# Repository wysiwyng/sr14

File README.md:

sr14
====

this will be the repo for the student robotics 2014 competition (http://srobo.org) of team MaI Senior (http://srobo.org/teams/MAI)

here all external hardware and software files will be stored, the main program code will be made public after the competition is over.

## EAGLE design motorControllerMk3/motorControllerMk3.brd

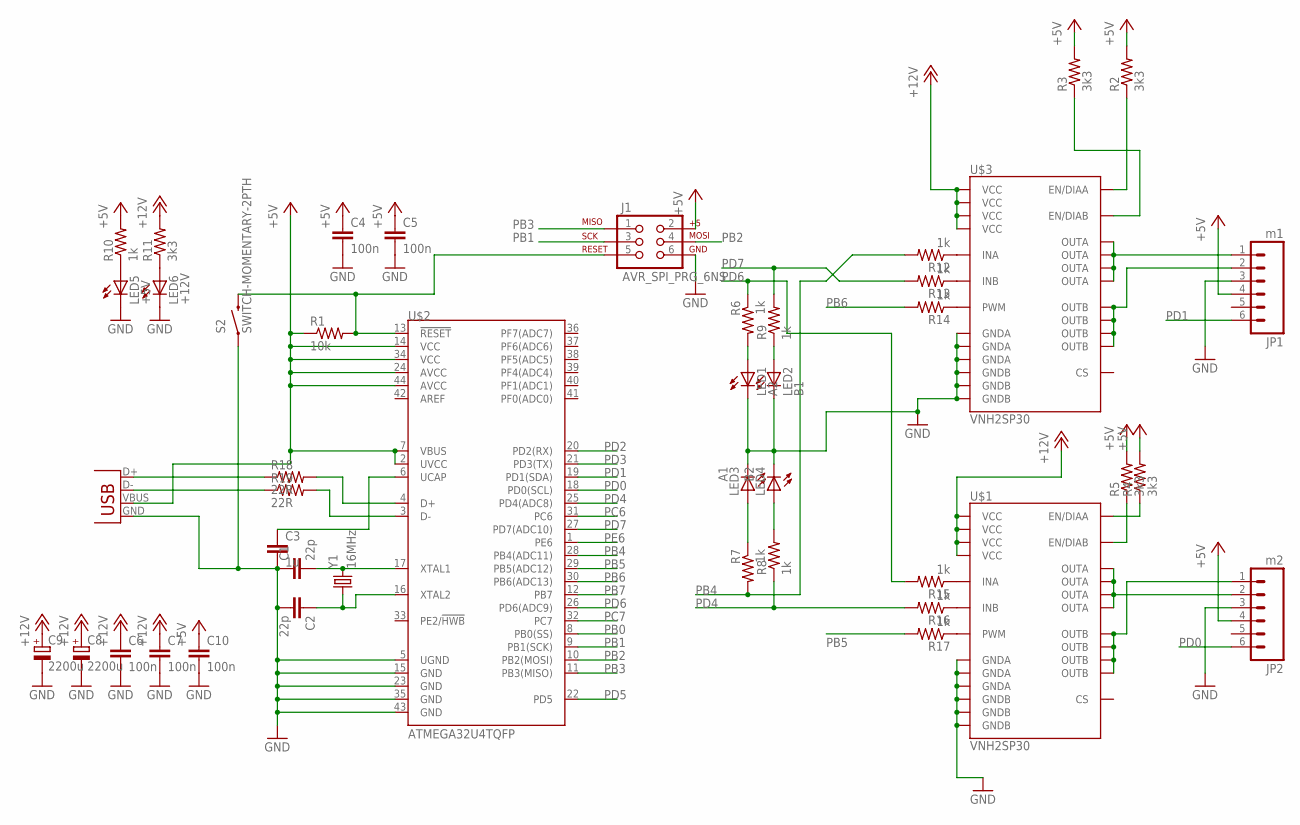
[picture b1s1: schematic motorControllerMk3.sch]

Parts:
C1, C2: 22p; 0805
C3: 1u; 0805
C4, C5, C6, C7, C10: 100n; 0805
C8, C9: 2200u; E5-8,5
J1: AVR_SPI_PRG_6NS; 2X3-NS
JP1: m1; 1X06
JP2: m2; 1X06
JP3: USB-SMD-NS; USB-MINIB-NOSTOP
LED1: A2; LED-1206
LED2: B1; LED-1206
LED3: A1; LED-1206
LED4: B2; LED-1206
LED5: +5V; LED-1206
LED6: +12V; LED-1206
R1: 10k; 0805
R2, R3, R4, R5, R11: 3k3; 0805
R6, R7, R8, R9, R10, R12, R13, R14, R15, R16, R17: 1k; 0805
R18, R19: 22R; 0805
S2: SWITCH-MOMENTARY-2PTH; TACTILE-PTH
U$1, U$3: VNH2SP30
U$2: ATMEGA32U4TQFP; SPARKFUN-DIGITALIC_TQFP44
Y1: 16MHz; HC49US

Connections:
+5V: C4.1, C5.1, C10.1, J1.2, JP1.4, JP2.4, JP3.VBUS, R1.1, R2.2, R3.2, R4.2, R5.2, R10.2, U$2.2 (UVCC), U$2.7 (VBUS), U$2.14 (VCC), U$2.24 (AVCC), U$2.34 (VCC), U$2.44 (AVCC)
+12V: C6.1, C7.1, C8.+, C9.+, R11.2, U$1.3 (VCC), U$1.13 (VCC), U$1.23 (VCC), U$1.SLUG1 (VCC), U$3.3 (VCC), U$3.13 (VCC), U$3.23 (VCC), U$3.SLUG1 (VCC)
GND: C1.1, C2.2, C3.2, C4.2, C5.2, C6.2, C7.2, C8.-, C9.-, C10.2, J1.6, JP1.3, JP2.3, JP3.GND, LED1.C, LED2.C, LED3.C, LED4.C, LED5.C, LED6.C, S2.1, U$1.18 (GNDB), U$1.19 (GNDB), U$1.20 (GNDB), U$1.26 (GNDA), U$1.27 (GNDA), U$1.28 (GNDA), U$2.5 (UGND), U$2.15 (GND), U$2.23 (GND), U$2.35 (GND), U$2.43 (GND), U$3.18 (GNDB), U$3.19 (GNDB), U$3.20 (GNDB), U$3.26 (GNDA), U$3.27 (GNDA), U$3.28 (GNDA)
unnamed: R15.1, U$1.5 (INA)
unnamed: C2.1, U$2.16 (XTAL2), Y1.1
unnamed: C1.2, U$2.17 (XTAL1), Y1.2
unnamed: C3.1, U$2.6 (UCAP)
unnamed: R16.1, U$1.11 (INB)
unnamed: R17.1, U$1.8 (PWM)
unnamed: R5.1, U$1.10 (EN/DIAB)
unnamed: R4.1, U$1.6 (EN/DIAA)
unnamed: R12.1, U$3.5 (INA)
unnamed: R18.2, U$2.4 (D+)
unnamed: R19.2, U$2.3 (D-)
unnamed: R13.1, U$3.11 (INB)
unnamed: R14.1, U$3.8 (PWM)
unnamed: JP3.D+, R18.1
unnamed: JP3.D-, R19.1
unnamed: LED3.A, R7.1
unnamed: R3.1, U$3.10 (EN/DIAB)
unnamed: LED1.A, R6.2
unnamed: R2.1, U$3.6 (EN/DIAA)
unnamed: LED4.A, R8.2
unnamed: LED5.A, R10.1
unnamed: LED6.A, R11.1
unnamed: LED2.A, R9.1
unnamed: J1.5, R1.2, S2.3 (2), U$2.13 (!RESET)
OUTA1: JP1.1, U$3.1 (OUTA), U$3.25 (OUTA), U$3.30 (OUTA), U$3.SLUG3 (OUTA)
OUTA2: JP2.2, U$1.1 (OUTA), U$1.25 (OUTA), U$1.30 (OUTA), U$1.SLUG3 (OUTA)
OUTB1: JP1.2, U$3.15 (OUTB), U$3.16 (OUTB), U$3.21 (OUTB), U$3.SLUG2 (OUTB)
OUTB2: JP2.1, U$1.15 (OUTB), U$1.16 (OUTB), U$1.21 (OUTB), U$1.SLUG2 (OUTB)
PB0: U$2.8 (PB0(SS))
PB1: J1.3, U$2.9 (PB1(SCK))
PB2: J1.4, U$2.10 (PB2(MOSI))
PB3: J1.1, U$2.11 (PB3(MISO))
PB4: R7.2, R12.2, U$2.28 (PB4(ADC11))
PB5: R17.2, U$2.29 (PB5(ADC12))
PB6: R14.2, U$2.30 (PB6(ADC13))
PB7: U$2.12 (PB7)
PC6: U$2.31 (PC6)
PC7: U$2.32 (PC7)
PD0: JP2.6, U$2.18 (PD0(SCL))
PD1: JP1.6, U$2.19 (PD1(SDA))
PD2: U$2.20 (PD2(RX))
PD3: U$2.21 (PD3(TX))
PD4: R8.1, R16.2, U$2.25 (PD4(ADC8))
PD5: U$2.22 (PD5)
PD6: R6.1, R15.2, U$2.26 (PD6(ADC9))
PD7: R9.2, R13.2, U$2.27 (PD7(ADC10))
PE6: U$2.1 (PE6)

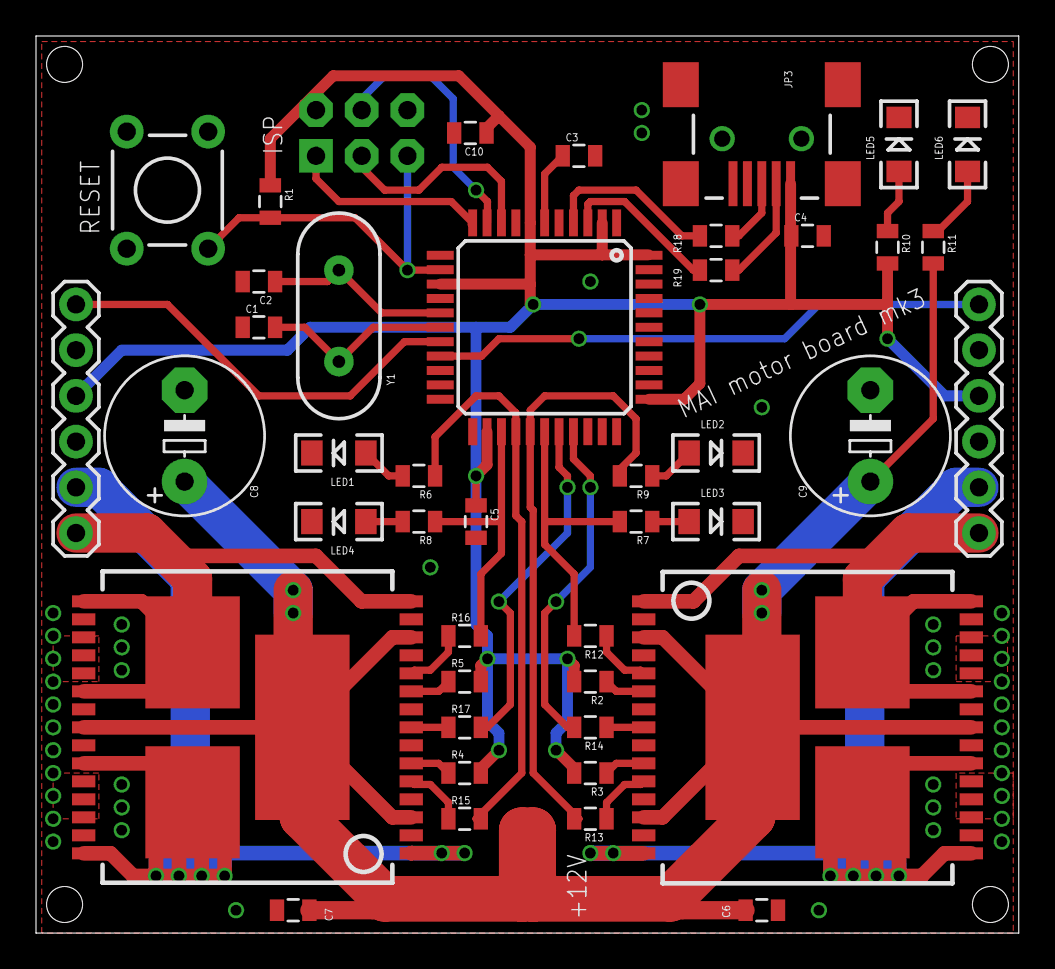
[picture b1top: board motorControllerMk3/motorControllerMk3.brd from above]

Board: 2 copper layers, 54.6 x 49.8 mm, 44 parts (0 on the bottom side), 42 nets.

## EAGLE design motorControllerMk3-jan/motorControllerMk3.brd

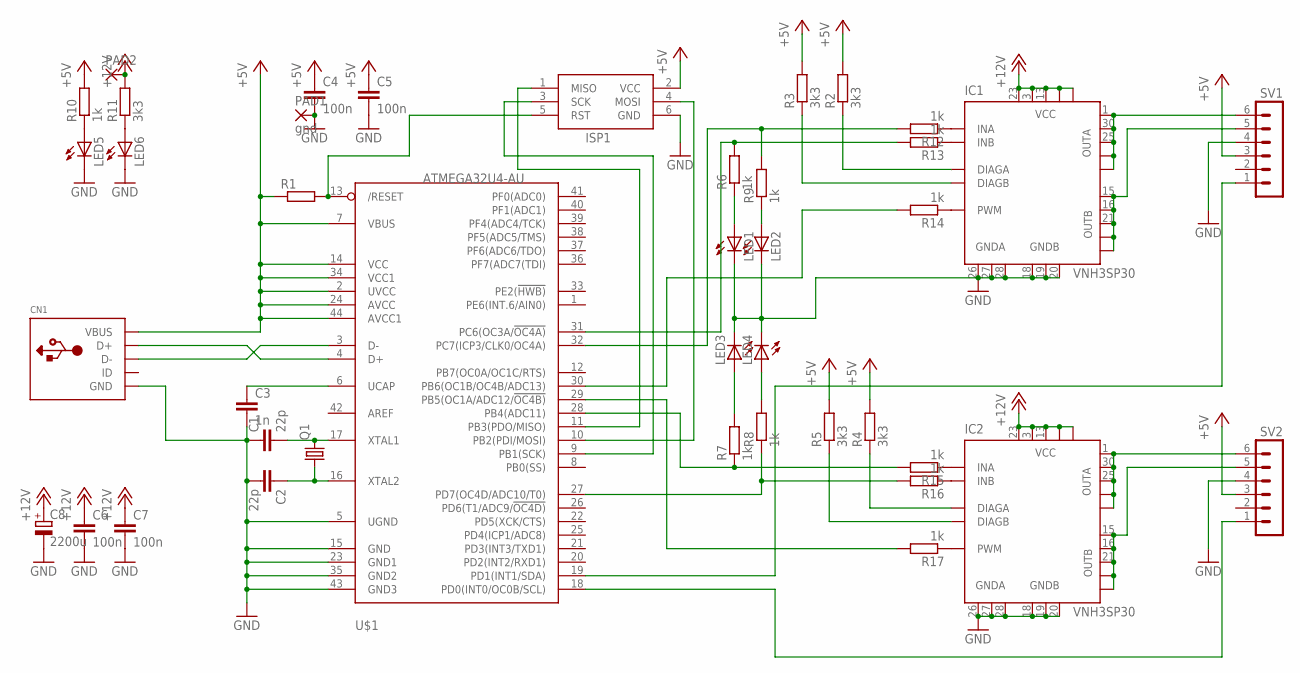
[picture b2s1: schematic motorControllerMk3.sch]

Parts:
C1, C2: 22p; C0805K
C3: 1n; C0805K
C4, C5, C6, C7: 100n; C0805K
C8: 2200u; E5-8,5
CN1: USBMINIB; USB-MINIB
IC1, IC2: VNH3SP30; MULTIPOWERSO-30
ISP1: AVRISP-6; AVRISP
LED1, LED2, LED3, LED4, LED5, LED6: LEDSML1206; SML1206
PAD1: gnd; 3,81/1,1
PAD2: 3,81/1,1
Q1: CRYSTALHC49U-V; HC49U-V
R1: R-EU_M0805; M0805
R2, R3, R4, R5, R11: 3k3; M0805
R6, R7, R8, R9, R10, R12, R13, R14, R15, R16, R17: 1k; M0805
SV1, SV2: MA06-1
U$1: ATMEGA32U4-AU; TQFP44

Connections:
+5V: C4.1, C5.1, CN1.VBUS, ISP1.2 (VCC), R1.1, R2.2, R3.2, R4.2, R5.2, R10.2, SV1.3, SV2.3, U$1.2 (UVCC), U$1.7 (VBUS), U$1.14 (VCC), U$1.24 (AVCC), U$1.34 (VCC1), U$1.44 (AVCC1)
+12V: C6.1, C7.1, C8.+, IC1.3 (VCC), IC1.13 (VCC), IC1.23 (VCC), IC1.VCC, IC1.VCC@1 (VCC), IC2.3 (VCC), IC2.13 (VCC), IC2.23 (VCC), IC2.VCC, IC2.VCC@1 (VCC), PAD2.1, R11.2
GND: C1.1, C2.2, C3.2, C4.2, C5.2, C6.2, C7.2, C8.-, CN1.GND, IC1.18 (GNDB), IC1.19 (GNDB), IC1.20 (GNDB), IC1.26 (GNDA), IC1.27 (GNDA), IC1.28 (GNDA), IC2.18 (GNDB), IC2.19 (GNDB), IC2.20 (GNDB), IC2.26 (GNDA), IC2.27 (GNDA), IC2.28 (GNDA), ISP1.6 (GND), LED1.C, LED2.C, LED3.C, LED4.C, LED5.C, LED6.C, PAD1.1, SV1.4, SV2.4, U$1.5 (UGND), U$1.15 (GND), U$1.23 (GND1), U$1.35 (GND2), U$1.43 (GND3)
unnamed: ISP1.3 (SCK), U$1.9 (PB1(SCK))
unnamed: C2.1, Q1.1, U$1.16 (XTAL2)
unnamed: C1.2, Q1.2, U$1.17 (XTAL1)
unnamed: C3.1, U$1.6 (UCAP)
unnamed: ISP1.5 (RST), R1.2, U$1.13 (/RESET)
unnamed: ISP1.4 (MOSI), U$1.10 (PB2(PDI/MOSI))
unnamed: ISP1.1 (MISO), U$1.11 (PB3(PDO/MISO))
unnamed: R17.2, U$1.29 (PB5(OC1A/ADC12/!OC4B))
unnamed: R14.2, U$1.30 (PB6(OC1B/OC4B/ADC13))
unnamed: CN1.D+, U$1.4 (D+)
unnamed: CN1.D-, U$1.3 (D-)
unnamed: SV2.1, U$1.18 (PD0(INT0/OC0B/SCL))
unnamed: IC1.1 (OUTA), IC1.25 (OUTA), IC1.30 (OUTA), IC1.OUTA, IC1.OUTA@1 (OUTA), SV1.6
unnamed: IC1.15 (OUTB), IC1.16 (OUTB), IC1.21 (OUTB), IC1.OUTB, IC1.OUTB@1 (OUTB), SV1.5
unnamed: IC2.15 (OUTB), IC2.16 (OUTB), IC2.21 (OUTB), IC2.OUTB, IC2.OUTB@1 (OUTB), SV2.5
unnamed: IC2.1 (OUTA), IC2.25 (OUTA), IC2.30 (OUTA), IC2.OUTA, IC2.OUTA@1 (OUTA), SV2.6
unnamed: SV1.1, U$1.19 (PD1(INT1/SDA))
unnamed: IC2.6 (DIAGA), R4.1
unnamed: IC2.10 (DIAGB), R5.1
unnamed: IC1.6 (DIAGA), R2.1
unnamed: IC1.10 (DIAGB), R3.1
unnamed: LED4.A, R8.2
unnamed: R8.1, R16.2, U$1.27 (PD7(OC4D/ADC10/T0))
unnamed: R7.1, R15.2, U$1.28 (PB4(ADC11))
unnamed: R6.2, R13.2, U$1.31 (PC6(OC3A/!OC4A))
unnamed: R9.2, R12.2, U$1.32 (PC7(ICP3/CLK0/OC4A))
unnamed: LED3.A, R7.2
unnamed: LED5.A, R10.1
unnamed: LED6.A, R11.1
unnamed: LED2.A, R9.1
unnamed: LED1.A, R6.1
unnamed: IC1.5 (INA), R12.1
unnamed: IC1.11 (INB), R13.1
unnamed: IC1.8 (PWM), R14.1
unnamed: IC2.5 (INA), R15.1
unnamed: IC2.11 (INB), R16.1
unnamed: IC2.8 (PWM), R17.1

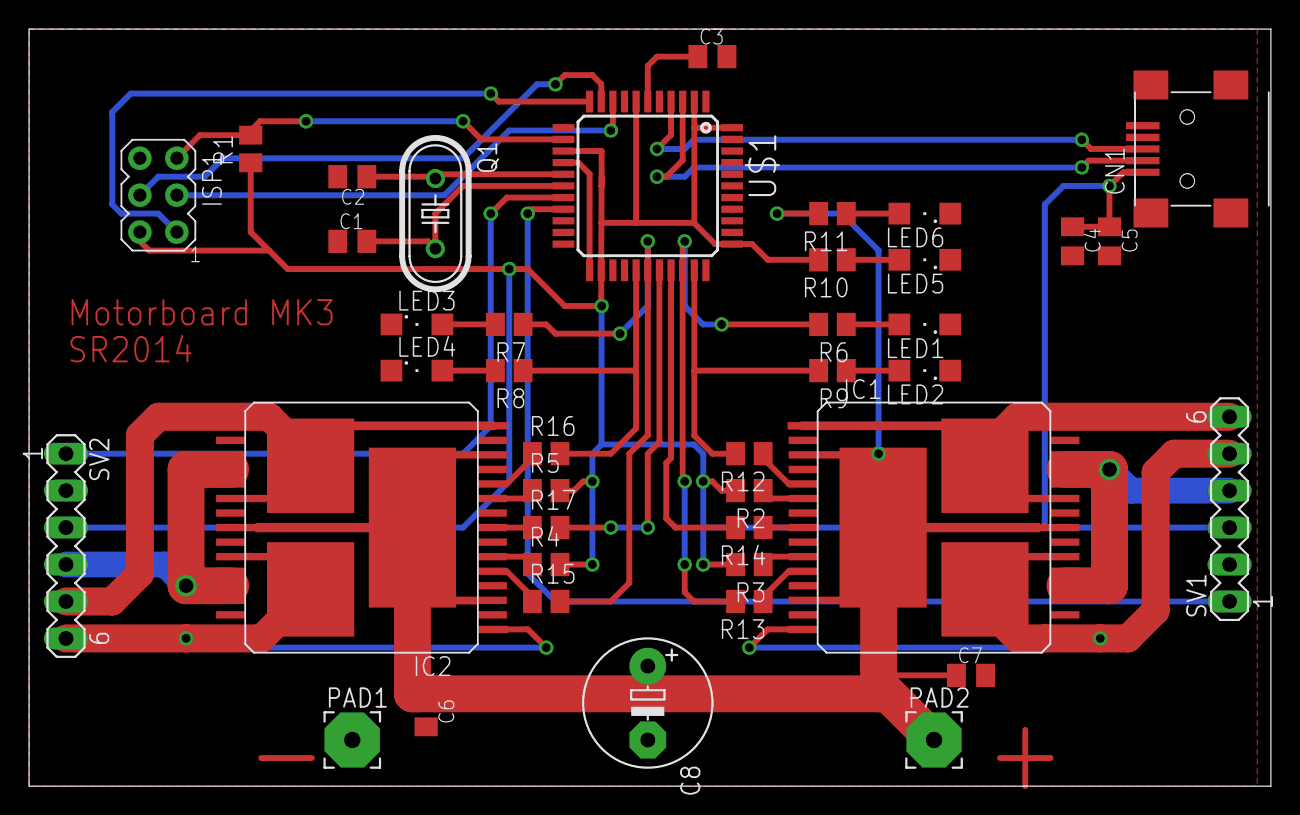
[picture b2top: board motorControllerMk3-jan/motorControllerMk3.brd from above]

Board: 2 copper layers, 85.4 x 52.1 mm, 41 parts (0 on the bottom side), 40 nets.

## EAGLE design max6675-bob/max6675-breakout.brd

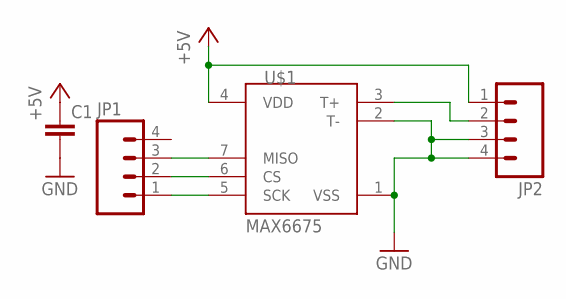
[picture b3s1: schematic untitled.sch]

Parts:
C1: CAP0805; 0805
JP1, JP2: M04LONGPADS; 1X04_LONGPADS
U$1: MAX6675; SO08-MAX6675

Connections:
+5V: C1.1, JP2.1, U$1.4 (VDD)
GND: C1.2, JP2.3, JP2.4, U$1.1 (VSS), U$1.2 (T-)
unnamed: JP1.1, U$1.5 (SCK)
unnamed: JP1.3, U$1.7 (MISO)
unnamed: JP1.2, U$1.6 (CS)
unnamed: JP2.2, U$1.3 (T+)

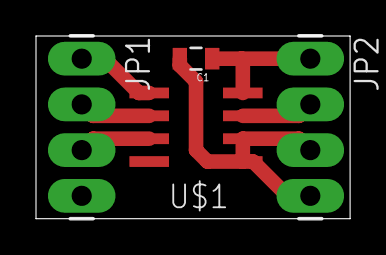
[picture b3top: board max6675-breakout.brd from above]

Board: 2 copper layers, 17.4 x 10.2 mm, 4 parts (0 on the bottom side), 6 nets.

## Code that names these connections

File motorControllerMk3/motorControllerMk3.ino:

/*
#    Copyright (C) 2105  wysiwyng
#
#    This program is free software: you can redistribute it and/or modify
#    it under the terms of the GNU General Public License as published by
#    the Free Software Foundation, either version 3 of the License, or
#    (at your option) any later version.
#
#    This program is distributed in the hope that it will be useful,
#    but WITHOUT ANY WARRANTY; without even the implied warranty of
#    MERCHANTABILITY or FITNESS FOR A PARTICULAR PURPOSE.  See the
#    GNU General Public License for more details.
#
#    You should have received a copy of the GNU General Public License
#    along with this program.  If not, see <http://www.gnu.org/licenses/>.
*/

#include <TimerThree.h>
#include <avr/wdt.h>
#include <SoftwareSerial.h>

#define debug

#define VERSION 132

#define pi 3.14159265

#define encoder0pinA PIN_D0
#define encoder1pinA PIN_D1

#define dir0A PIN_D6     //PD6
#define dir0B PIN_D4     //PD4

#define dir1A PIN_B4     //PB4
#define dir1B PIN_D7     //PD7

#define pwm0 PIN_B5
#define pwm1 PIN_B6

#define wheelDiameter 11
#define wheelDistance 46
#define cpr 1600

#define cpcm cpr/(wheelDiameter*pi)
#define cmpd (wheelDistance*pi)/360

#define maxFaults 40
#define minSpeed 10

volatile unsigned long c0 = 0;
volatile unsigned long c1 = 0;

volatile unsigned long dist = 0;

byte duration0 = 0;//Encoder0 number of pulses
byte duration1 = 0;//Encoder1 number of pulses

char setPoint = 0; // 0 would be straight ahead
#define p 10 // needs tuning
char error = 0;
byte speed = 0; // set the speed of which the vechicle should move
int output = 0;

byte faultCount = 0;

volatile byte status = 0;

#define get_completed status & (1 << 0)
#define get_fault status & (1 << 1)
#define get_preFault status & (1 << 2)
#define get_wait status & (1 << 3)
#define get_off status & (1 << 4)

#define set_completed status |= (1 << 0)
#define set_fault status |= (1 << 1)
#define set_preFault status |= (1 << 2)
#define set_wait status |= (1 << 3)
#define set_off status |= (1 << 4)

#define reset_completed status &= ~(1 << 0)
#define reset_fault status &= ~(1 << 1)
#define reset_preFault status &= ~(1 << 2)
#define reset_wait status &= ~(1 << 3)
#define reset_off status &= ~(1 << 4)

byte counter = 0;
byte vars[5] = {
  0, 0, 0, 0, 0};

SoftwareSerial debugSer(MISO, MOSI); //rx tx

void setup()
{
  MCUSR &= ~(1 << WDRF);
  wdt_disable();

  DDRD |= ((1 << 4) | (1 << 6) | (1 << 7));
  DDRB |= ((1 << 4) | (1 << 5) | (1 << 6));

  PORTD &= ~((1 << 4) | (1 << 6) | (1 << 7));
  PORTB &= ~((1 << 4) | (1 << 5) | (1 << 6));

  Serial.begin(115200); //Initialize the serial port

#ifdef debug
  debugSer.begin(9600);
#endif

  attachInterrupt(0, wheelSpeed0, CHANGE);
  attachInterrupt(1, wheelSpeed1, CHANGE);

  Timer3.initialize(20000);
  Timer3.attachInterrupt(timer3_int);
  Timer3.start();

  PORTD |= ((1 << 4) | (1 << 6) | (1 << 7));
  PORTB |= (1 << 4);
  delay(500);
  PORTD &= ~((1 << 4) | (1 << 6) | (1 << 7));
  PORTB &= ~(1 << 4);

#ifdef debug
  debugSer.println("ready");
#endif

  PORTB |= ((1 << 5) | (1 << 6));
}

void loop()
{
  if(debugSer.available())
  {
    byte rec = debugSer.read();
    if(rec == 's')
    {
      speed = 0;
      motorsBrake();
    }
    else
    {
      enableTimers();
      switch(rec)
      {
      case 'w':
        speed = 255;
        PORTD &= ~(1 << 6);
        PORTD |= ((1 << 4) | (1 << 7));
        PORTB &= ~(1 << 4);
        break;
      case 'x':
        speed = 255;
        PORTD |= (1 << 6);
        PORTD &= ~((1 << 4) | (1 << 7));
        PORTB |= (1 << 4);
        break;
      case 'a':
        speed = 130;
        PORTD &= ~(1 << 4);
        PORTD |= ((1 << 6) | (1 << 7));
        PORTB &= ~(1 << 4);
        break;
      case 'd':
        speed = 130;
        PORTD |= (1 << 4);
        PORTD &= ~((1 << 6) | (1 << 7));
        PORTB |= (1 << 4);
        break;
      }
    }
  }
  if(Serial.available())
  {
    byte rec = Serial.read();

#ifdef debug
    debugSer.print("in:");
    debugSer.print(rec);
    debugSer.print("\rc:");
    debugSer.print(counter);
    debugSer.print("\r");
#endif

    if(counter == 0)
    {
      switch(rec)
      {
      case 'v':
        Serial.write(VERSION);
        break;
      case '$':
        counter = 1;
        break;
      }
    }
    else if(counter > 0)
    {
      vars[counter - 1] = rec;
      counter++;
    }
    if(counter == 6)
    {
      counter = 0;
      speed = vars[1];
      setPoint = vars[2];

#ifdef debug
      debugSer.print("compl\r");
      debugSer.print(vars[0]);
      debugSer.print("\r");
      debugSer.print(speed);
      debugSer.print("\r");
      debugSer.print(setPoint);
      debugSer.print("\r");
      debugSer.print(word(vars[3], vars[4]));
      debugSer.print("\r");
#endif

      if(vars[0] & (1 << 0))
      {
        motorsBrake();
      }
      else if(speed == 0)
      {
        motorsFloat();
      }
      else 
      {
        if(vars[0] & (1 << 1))
        {
          dist = word(vars[3], vars[4]);
          dist = dist * cmpd;
          if(dist < 1 && word(vars[3], vars[4]) > 0) dist = 1;
          setPoint = 0;
          if(vars[0] & (1 << 2))
          {
            PORTD |= (1 << 4);
            PORTD &= ~((1 << 6) | (1 << 7));
            PORTB |= (1 << 4);
          }
          else
          {
            PORTD &= ~(1 << 4);
            PORTD |= ((1 << 6) | (1 << 7));
            PORTB &= ~(1 << 4);
          }
        }
        else
        {
          dist = word(vars[3], vars[4]);
          if(vars[0] & (1 << 2))
          {
            PORTD &= ~(1 << 6);
            PORTD |= ((1 << 4) | (1 << 7));
            PORTB &= ~(1 << 4);
          }
          else if (!(vars[0] & (1 << 2)))
          {
            PORTD |= (1 << 6);
            PORTD &= ~((1 << 4) | (1 << 7));
            PORTB |= (1 << 4);
          }
        }
        enableTimers();
        c0 = 0;
        c1 = 0;
      }

      if(dist > 0) reset_completed;
      else set_completed;

      set_wait;
      reset_fault;

#ifdef debug
      debugSer.print("wait\r");
#endif
    }
  }
  if(!get_completed && get_wait)
  {
    checkRev();
  }
  else if(get_completed && get_wait)
  {
#ifdef debug
    debugSer.print("done\r");
#endif
    Serial.print('$');
    if(get_fault) bitClear(vars[0], 3);
    Serial.write(vars[0]);
    Serial.write(vars[1]);
    Serial.write(vars[2]);
    Serial.write(vars[3]);
    Serial.write(vars[4]);
    reset_wait;
  }
}

void checkRev()
{
  if(dist == 0 || speed == 0)
  {
    return;
  }
  if(c0 >= (dist * cpcm) || c1 >= (dist * cpcm))
  {
    motorsBrake();
    resetVars();
  }
}

void timer3_int()
{
  if((duration0 < minSpeed || duration1 < minSpeed) && speed > 0)
  {
    if(get_preFault) faultCount++;
    else 
    {
      set_preFault;
      faultCount = 0;
    }
  }
  else reset_preFault;

  if(faultCount > maxFaults)
  {
    motorsBrake();
    resetVars();
    faultCount = 0;
    set_fault;
  }
  else
  {
    pReg();
    checkRev();
  }
}

void enableTimers()
{
  reset_off;
  TCCR1A |= ((1 << COM1A1) | (1 << COM1B1));
}  

void motorsBrake()
{
  motorsOff();
  PORTB |= ((1 << 5) | (1 << 6));
  OCR1A = 0;
  OCR1B = 0;
}

void motorsFloat()
{
  motorsOff();
  PORTB &= ~((1 << 5) | (1 << 6));
  OCR1A = 0;
  OCR1B = 0;
}

void motorsOff()
{
  if(get_off) return;
  set_off;
  if((PORTD & 0xC0) == 0xC0) PORTD &= ~0xC0;
  else if((PORTD & 0x90) == 0x90) PORTD &= ~0x90;
  else if((PORTD & 0xC0) == 0) PORTD |= 0xC0;
  else if((PORTD & 0x90) == 0) PORTD |= 0x90;
  TCCR1A &= ~((1 << COM1A1) | (1 << COM1B1));
}

void resetVars()
{
  speed = 0;
  setPoint = 0;
  dist = 0;
  set_completed;
}

void pReg()
{
  if(speed == 0) return;
  noInterrupts(); // Disable interrupts, no need to slow down the P regulator
  if(setPoint != 0)
  {
    output = map(setPoint, -100, 100, -speed, speed);
  }
  else
  {
    output = (duration0 - duration1) * p;
  }
  if(speed - output < 0) output = speed;
  if(speed + output < 0) output = -speed;
  //Serial.println(output,DEC);
  int temp;
  if(output >= 0) // its turning left of the setpoint, reduce pwm0 (right motor) pin 10 = OCR1B pin 11 = OCR2A
  {
    temp = speed - output;
    OCR1B = speed;
    OCR1A = temp; // Subtract the error value multiplied by Kp from pwm0
  }
  else // turning right of our setpoint, reduce pwm1
  {
    temp = speed + output;
    OCR1B = temp;
    OCR1A = speed;
  }
  duration0 = 0;
  duration1 = 0;
  interrupts(); //Enable interrupts again
}

void wheelSpeed0()
{
  duration0++;
  c0++;
}

void wheelSpeed1()
{
  duration1++;
  c1++;
}

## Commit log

2014-01-08 added ruggeduino
2014-01-08 finally works
2014-01-09 added new position, fixed dead zones
2014-01-09 added mk2 motorcontroller files
2014-01-10 added mk3 motor controller
2014-01-12 developing schematics
2014-01-12 updated gitignore to ignore eagle temp files
2014-01-12 added board layout file
2014-01-14 deleted useless files, playing around with layout
2014-01-16 further layouting
2014-01-17 finished layout
2014-01-17 added another layout
2014-01-18 finalizing layout
2014-01-18 generating gerbers
2014-01-18 deleting unused files
2014-01-18 now fits onto 5x10 cm pcb
2014-01-18 making pcb smaller
2014-01-19 fixed mistakes in layout, added usb resistors
2014-01-19 more space on crystal
2014-01-19 changed some traces to be shorter
2014-01-19 fixed wrong angles
2014-01-19 making ground plane bigger
2014-01-19 making better silkscreen
2014-01-20 optimizing ground plane and silk screen
2014-01-20 added mounting holes
2014-01-20 turned around some resistors to get better silkscreen
2014-01-20 added copyright
2014-01-20 now checking for top position
2014-01-26 added max6675 breakout board
2014-02-05 edited code for new motor board
2014-02-06 edited motor controller to notice blocking motors, added modified reflow oven code by rocket scream electronics
2014-02-07 added pid params for prepreheat phase, modified display output for 16x2 char lcd
2014-02-07 improved stall detection
2014-02-07 fixed display routines
2014-02-09 now using teensy libraries, stall detection fixed
2014-02-09 moved some variables to defines
2014-02-09 added version responses, set new wheel diameter
2014-02-09 speeding up motor switches
2014-02-09 changed wheel distance again
2014-02-09 added a breakout board for max6675
2014-02-09 added batch script for on-stick developing
2014-02-10 disabling wdt at start of code for cdc bootloader use
2014-02-11 moved reflow oven code to new repo
2014-02-11 cleaning up code
2014-02-11 further cleaning, changed startup blinking
2014-02-14 making code more stdc like as arduino is too slow
2014-02-15 further code optimizations
2014-02-19 added linux version of packing script
2014-03-01 fixed lift heights for faster lift
2014-04-04 added blinky lights
2014-04-07 fixed bugs in turn calculations
2014-04-09 added debugging via softserial
2014-04-21 added leduino and updated ruggeduino
2014-04-26 changed led pattern, added configwriter
2014-04-28 added sr14 competition code

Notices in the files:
motorControllerMk3/motorControllerMk3.brd:
(c) 2014 K. Emrich, J. Veeh
parts and their libraries:
SparkFun-AnalogIC: Licensing: CC v3.0 Share-Alike You are welcome to use this library for commercial purposes.
